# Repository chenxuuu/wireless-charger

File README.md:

# wireless-charger

use XKT-510

## Kicad libs

https://gitee.com/openLuat/kicad-symbols-libraries

https://github.com/chenxuuu/chenxuuu-kicad-lib

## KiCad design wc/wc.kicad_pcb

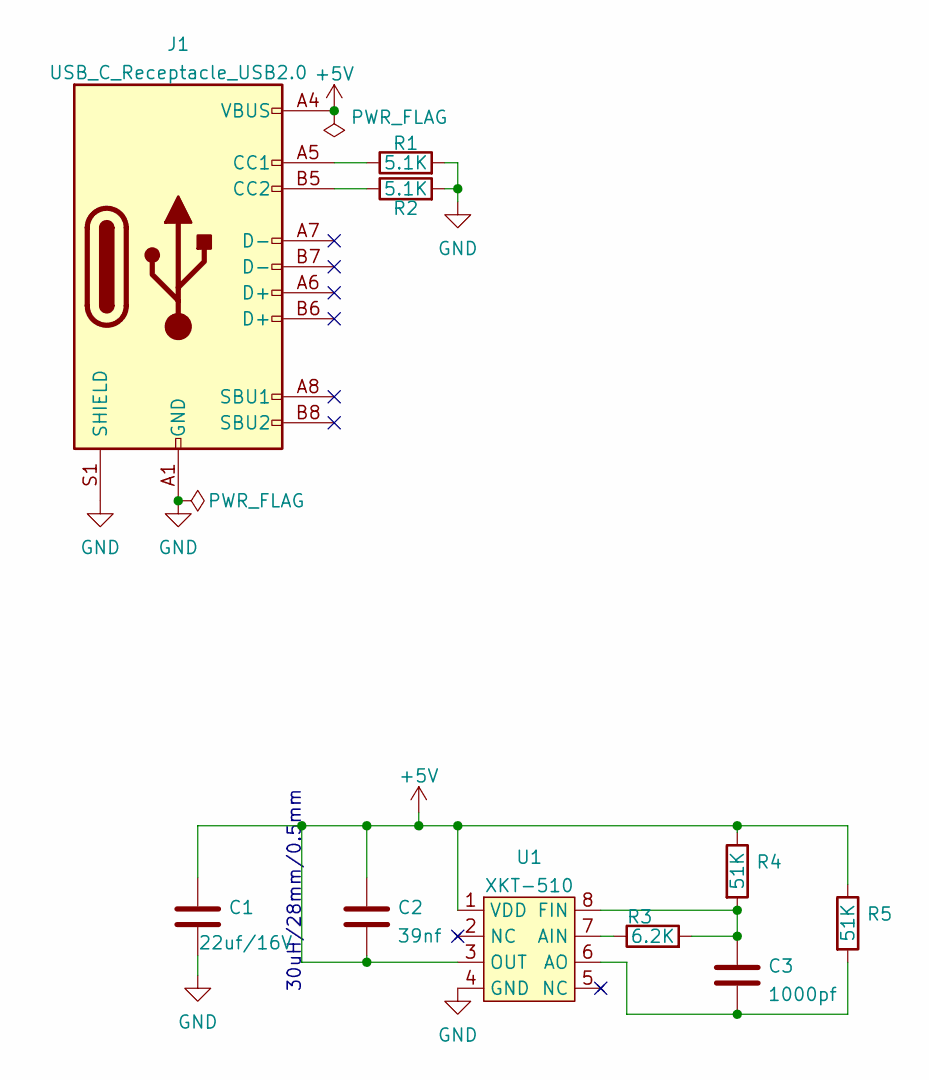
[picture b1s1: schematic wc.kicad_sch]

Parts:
C1: 22uf/16V; C_0805_2012Metric
C2: 39nf; C_0402_1005Metric
C3: 1000pf; C_0402_1005Metric
J1: USB_C_Receptacle_USB2.0; USB_C_Receptacle_Palconn_UTC16-G
R1, R2: 5.1K; R_0402_1005Metric
R3: 6.2K; R_0402_1005Metric
R4, R5: 51K; R_0402_1005Metric
U1: XKT-510; SOP-8_3.9x4.9mm_P1.27mm

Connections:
+5V: C1.1, C2.1, C2.2, J1.A4 (VBUS), J1.A9 (VBUS), J1.B4 (VBUS), J1.B9 (VBUS), R4.1, R5.1, U1.1 (VDD), U1.3 (OUT)
GND: C1.2, J1.A1 (GND), J1.A12 (GND), J1.B1 (GND), J1.B12 (GND), J1.S1 (SHIELD), R1.2, R2.2, U1.4 (GND)
unnamed: C3.1, R3.2, R4.2, U1.8 (FIN)
unnamed: C3.2, R5.2, U1.6 (AO)
unnamed: J1.A5 (CC1), R1.1
unnamed: J1.B5 (CC2), R2.1
unnamed: R3.1, U1.7 (AIN)

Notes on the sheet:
30uH/28mm/0.5mm

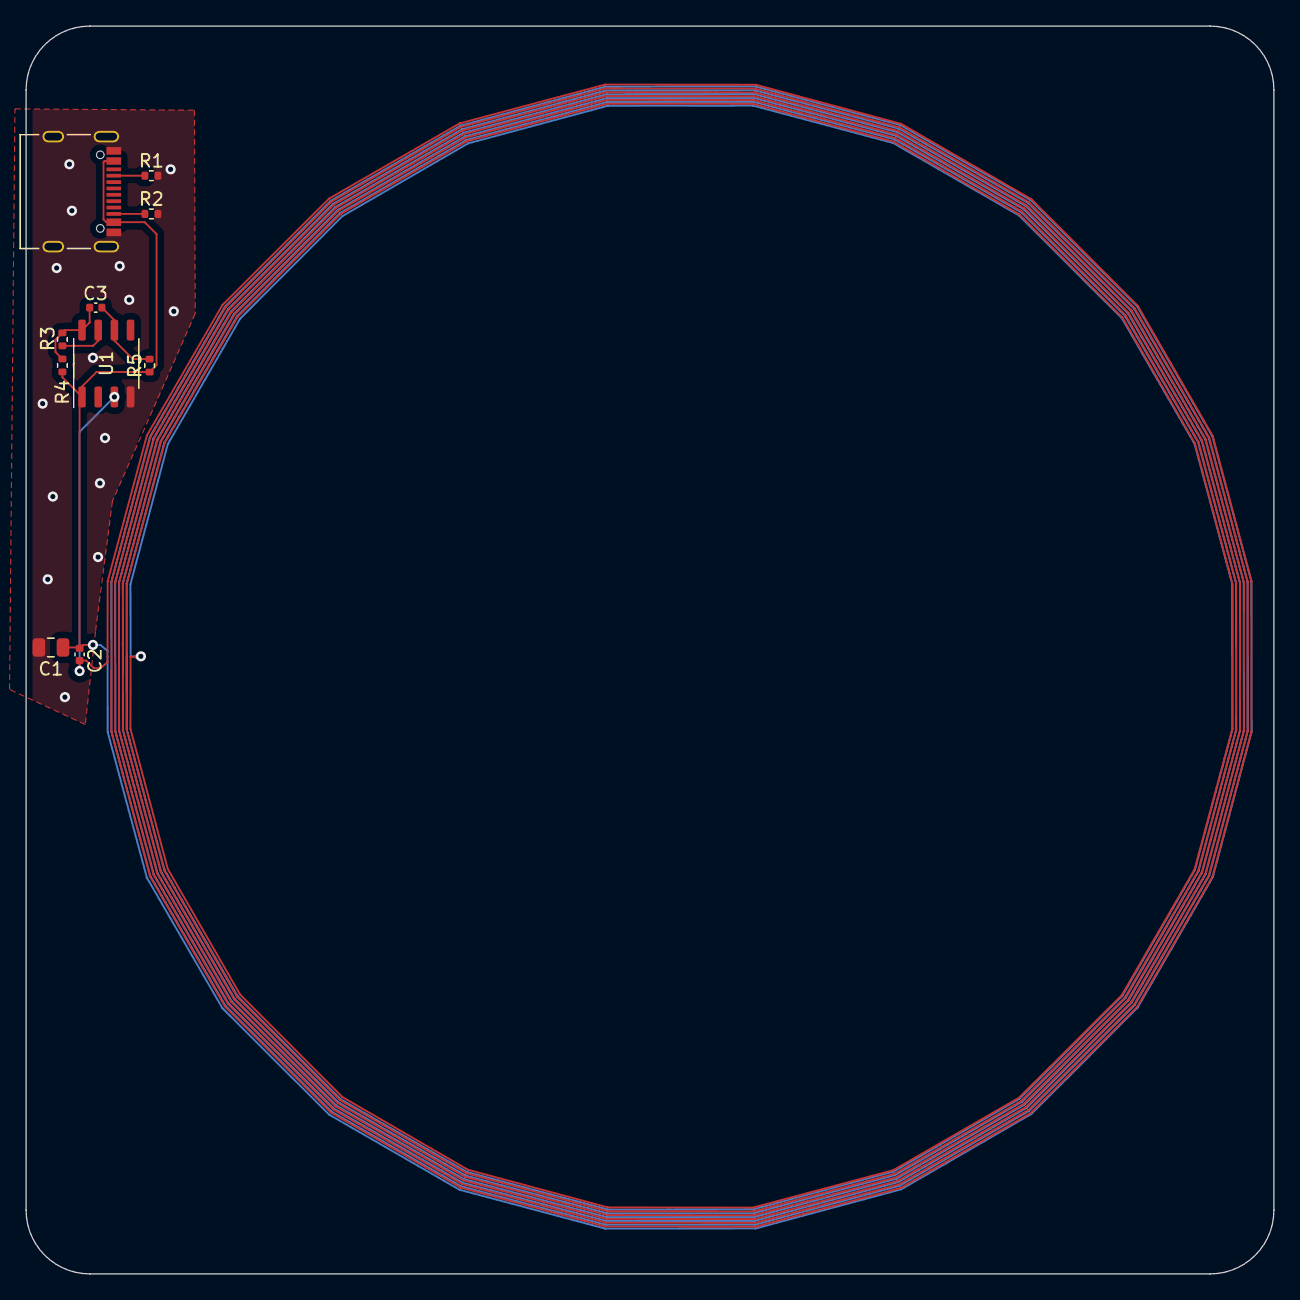
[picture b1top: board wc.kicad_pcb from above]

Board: 2 copper layers, 98.0 x 98.0 mm, 10 parts (0 on the bottom side), 7 nets.

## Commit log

2021-11-22 add: 画好了，打板试试
2021-11-22 update: 更新
2021-11-29 fix: 更正参数
